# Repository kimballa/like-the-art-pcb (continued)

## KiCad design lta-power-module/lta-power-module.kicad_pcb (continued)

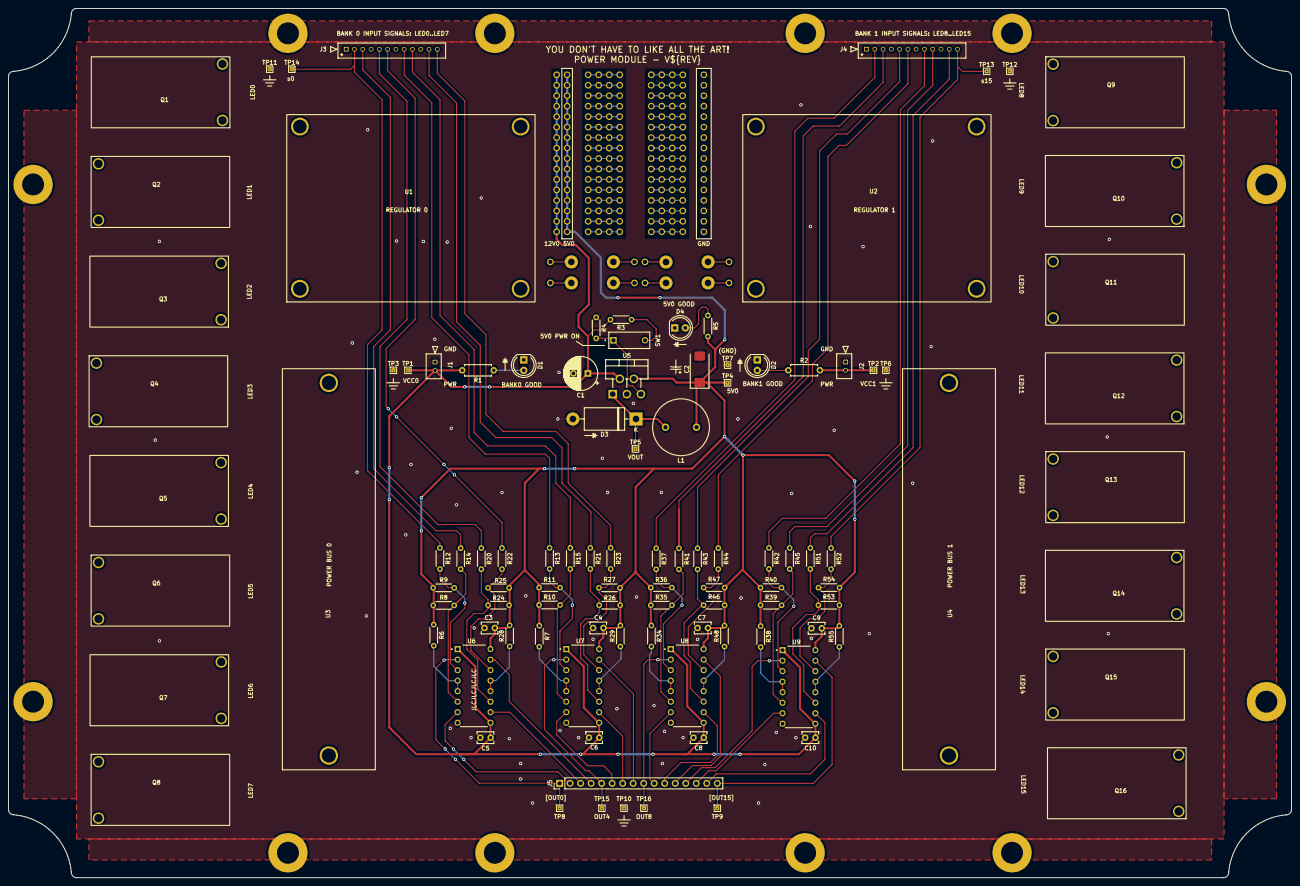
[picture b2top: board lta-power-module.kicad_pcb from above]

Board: 2 copper layers, 310.0 x 210.0 mm, 311 parts (0 on the bottom side), 106 nets.

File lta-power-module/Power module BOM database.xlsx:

Reference | Value | Footprint | Datasheet | Comment | MANUFACTURER | MPN | SPN | Supplier | Qty
C1 | 220u | Capacitor_THT:CP_Radial_D8.0mm_P3.50mm | https://content.kemet.com/datasheets/KEM_A4010_EST.pdf | 220u 20% 35V low-ESR (<=160mOhm), I_RMS>250mA aluminum | KEMET | EST227M035AG4AA | 399-6615-ND | DigiKey | 1
C2 | 68u | Capacitor_Tantalum_SMD:CP_EIA-7343-30_AVX-N_Pad2.25x2.55mm_HandSolder | https://datasheets.kyocera-avx.com/TPS.pdf | 68u 10% AVX TPS 20V low-ESR (<=150mOhm) solid tantalum; exact MPN | KYOCERA AVX | TPSD686M020R0150 | 478-9217-1-ND | DigiKey | 1
> C3-C10 | 1u | Capacitor_THT:C_Disc_D3.8mm_W2.6mm_P2.50mm | https://connect.kemet.com:7667/gateway/IntelliData-Component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 | 1u X7R 25V low-ESR THT | KEMET | C315C105K3R5TA7303 | 399-C315C105K3R5TA7303CT-ND | DigiKey | 8
D1 | PWR0 | Aaron_THT:LED_D5.0mm_SilkFix | https://cree-led.com/media/documents/C5SMF-RJF-RJE-GJF-GJE-B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 | Vf=2.0V I_test=20mA red LED 5mm THT | CreeLED | C5SMF-RJF-CT0W0BB1 | C5SMF-RJF-CT0W0BB1-ND | DigiKey | 1
D2 | PWR1 | Aaron_THT:LED_D5.0mm_SilkFix | https://cree-led.com/media/documents/C5SMF-RJF-RJE-GJF-GJE-B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 | Vf=2.0V I_test=20mA red LED 5mm THT | CreeLED | C5SMF-RJF-CT0W0BB1 | C5SMF-RJF-CT0W0BB1-ND | DigiKey | 1
D3 | SB530 | Diode_THT:D_DO-201AD_P15.24mm_Horizontal | https://www.vishay.com/docs/88721/sb520.pdf | 30V 5A Schottky diode, Vf <= 480mV. (Any SB530-xxx diode OK) | Vishay | SB530-E3/54 | SB530-E3/54GICT-ND | DigiKey | 1
D4 | 5V0PWR | Aaron_THT:LED_D5.0mm_SilkFix | https://cree-led.com/media/documents/C5SMF-RJF-RJE-GJF-GJE-B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 | Vf=2.0V I_test=20mA red LED 5mm THT | CreeLED | C5SMF-RJF-CT0W0BB1 | C5SMF-RJF-CT0W0BB1-ND | DigiKey | 1
> H1-H12 | MountingHole_Pad | MountingHole:MountingHole_5.3mm_M5_ISO7380_Pad | ~ | M5 screw mounting hole, ISO 7380 pad |  |  |  |  | 12
> J1, J2 | Molex-MicroLatch-53253-0270 | Aaron_THT:Molex-MicroLatch-53253-0270 | https://www.molex.com/webdocs/datasheets/pdf/en-us/053253027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 | 2-pin header for power (regulator out) | Molex | 532530270 | WM19004-ND | DigiKey | 2
> J3, J4 | Molex-MicroLatch-53253-1270 | Aaron_THT:Molex-MicroLatch-53253-1270 | https://www.molex.com/webdocs/datasheets/pdf/en-us/053253127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 | 12-pin signal connector | Molex | 532531270 | WM24308-ND | DigiKey | 2
J5 | Conn_01x16 | Connector_PinHeader_2.54mm:PinHeader_1x16_P2.54mm_Vertical | ~ | standard male 2.54mm gold THT header pin row | TE Connectivity AMP Connectors | 5-146858-1 | A105469CT-ND | DigiKey | 1
> J6, J8-J17, J19, J20, J22-J31, J34, J36-J45, J47, J48, J50-J59, J61-J69, J71,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 | Conn_01x01 | Aaron_Pads:1mm_PTH_No_Silk | ~ | standard 1mm PTH for prototyping |  |  |  |  | 184
> J18, J46, J60, J70, J98, J108, J122, J160 | Conn_01x01 | Aaron_Pads:1.6mm_PTH_No_Silk | ~ | larger 1.6mm holes for DO201 diodes, larger capacitors |  |  |  |  | 8
L1 | 150u | Aaron_THT:L_Radial_D13.5mm_P7.50mm | https://abracon.com/Magnetics/radial/AIUR-06.pdf | 150uH, Exact MFR/MPN required | Abracon LLC | AIUR-06-151K | 535-13029-ND | DigiKey | 1
> Q1-Q16 | Dual_MOSFET_Switch_Module | lta-power-footprints:Dual_MOSFET_Driver | https://protosupplies.com/product/high-power-dual-mosfet-swi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 | Dual MOSFET driver board w/ mounting holes |  |  | B07XJSRY6B | Amazon | 16
> R1, R2 | 1K, 1/4W | Resistor_THT:R_Axial_DIN0207_L6.3mm_D2.5mm_P7.62mm_Horizontal |  | 1K THT resistor; +/-5%; 1/4W | Stackpole | CF14JT1K00 | CF14JT1K00CT-ND | DigiKey | 2
> R3, R4 | 10K | Resistor_THT:R_Axial_DIN0204_L3.6mm_D1.6mm_P5.08mm_Horizontal | ~ | 10K THT resistor; +/-5%; 1/8W | Stackpole | CF18JT10K0 | CF18JT10K0CT-ND | DigiKey | 2
R5 | 330R | Resistor_THT:R_Axial_DIN0204_L3.6mm_D1.6mm_P5.08mm_Horizontal |  | 330R THT resistor; +/-5%; 1/8W | Stackpole | CF18JT330R | CF18JT330RCT-ND | DigiKey | 1
> R12-R15, R20-R23, R37, R41-R45, R51, R52 | 33R | Resistor_THT:R_Axial_DIN0204_L3.6mm_D1.6mm_P5.08mm_Horizontal | ~ | 33R THT resistor; +/-5%; 1/8W | Stackpole | CF18JT33R0 | CF18JT33R0CT-ND | DigiKey | 16
> R6, R7, R28, R29, R34, R38, R48, R55 | 220R | Resistor_THT:R_Axial_DIN0204_L3.6mm_D1.6mm_P5.08mm_Horizontal | ~ | 220R THT resistor; +/-5%; 1/8W | Stackpole | CF18JT220R | CF18JT220RCT-ND | DigiKey | 8
> R8-R11, R24-R27, R35, R36, R39, R40, R46, R47, R53, R54 | 2K2 | Resistor_THT:R_Axial_DIN0204_L3.6mm_D1.6mm_P5.08mm_Horizontal | ~ | 2K2 THT resistor; +/-5%; 1/8W | Stackpole | CF18JT2K20 | CF18JT2K20CT-ND | DigiKey | 16
SW1 | SW_SPST | Aaron_THT:CUI-DIP-SW_DS01-254-x-01xx | https://www.cuidevices.com/product/resource/ds01-254.pdf | Any 1x SPST THT dip switch w/ same footprint OK | CUI Devices | DS01-254-S-01BE | 2223-DS01-254-S-01BE-ND | DigiKey | 1
> TP1-TP16 | TestPoint_Flag | Aaron_THT:TestPoint_THTPad_1.0x1.0mm_Drill0.3mm | ~ |  |  |  |  |  | 16
> U1, U2 | DIYMORE_20A_Step_Down | lta-power-footprints:12V_regulator | https://www.amazon.com/dp/B07Y7YB14L?psc=1&ref=ppx_yo2ov_dt_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 |  | DIYMORE |  | B07Y7YB14L | Amazon | 2
> U3, U4 | OONO_16A_12pos_Terminal_Block | lta-power-footprints:12-way_power_distribution_bus | https://www.amazon.com/dp/B08TBXQ7H6?psc=1&smid=A2OVMUS055KM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 |  |  |  | B08TBXQ7H6 | Amazon | 2
U5 | LM2595T-5 | Aaron_THT:TO-220-5_P3.4x3.7mm_StaggerOdd_Lead3.8mm_Vertical-SilkFix | http://www.ti.com.cn/cn/lit/ds/symlink/lm2595.pdf | Exact MFR/MPN required | Texas Instruments | LM2595T-5.0/NOPB | LM2595T-5.0/NOPB-ND | DigiKey | 1
> U6-U9 | SN75374N | Aaron_TI_Parts:TI_N_R-PDIP-T16 | https://www.ti.com/lit/ds/symlink/sn75374.pdf |  | Texas Instruments | SN75374N | 296-34130-5-ND | DigiKey | 4

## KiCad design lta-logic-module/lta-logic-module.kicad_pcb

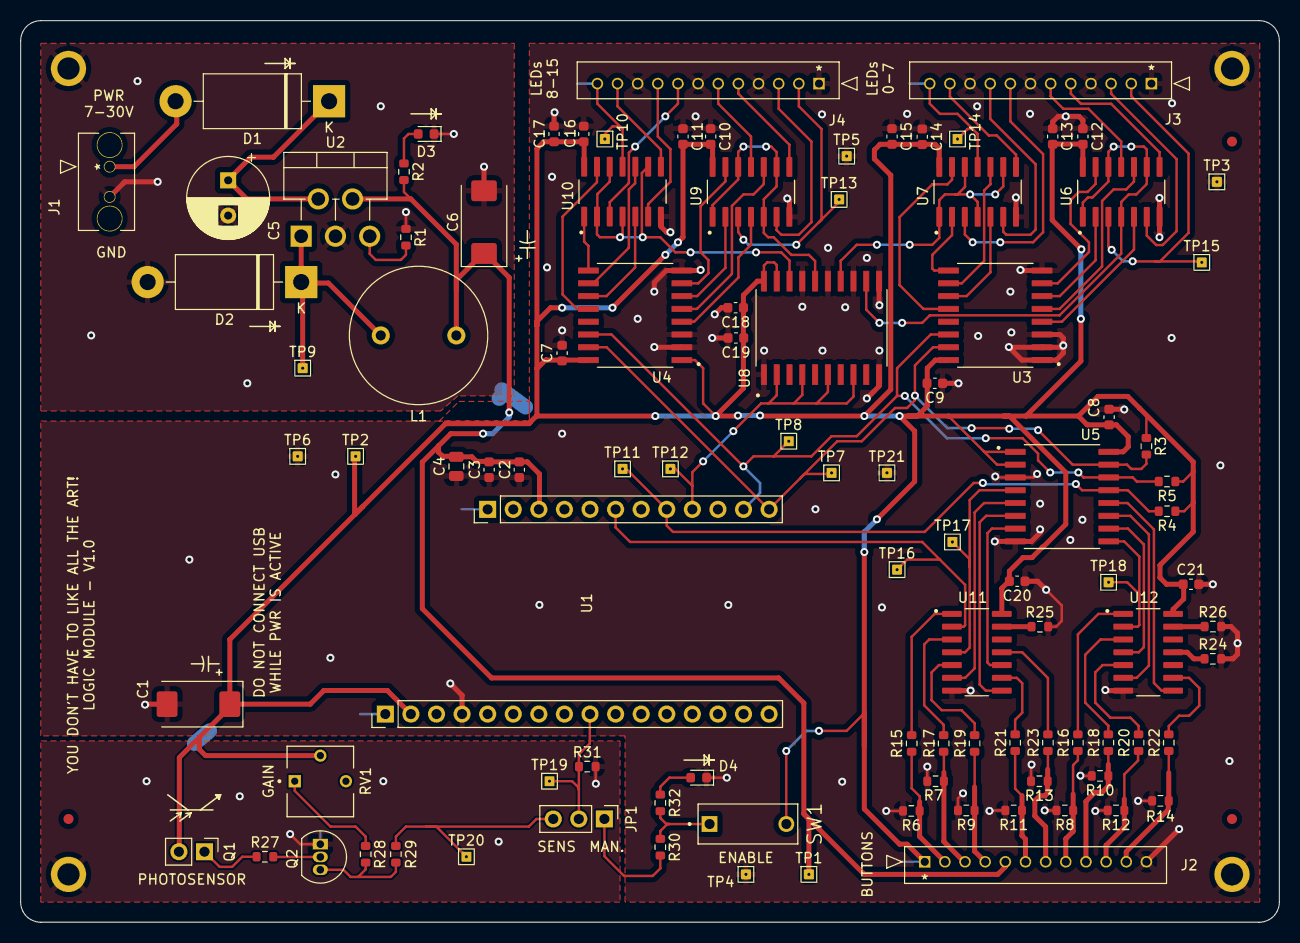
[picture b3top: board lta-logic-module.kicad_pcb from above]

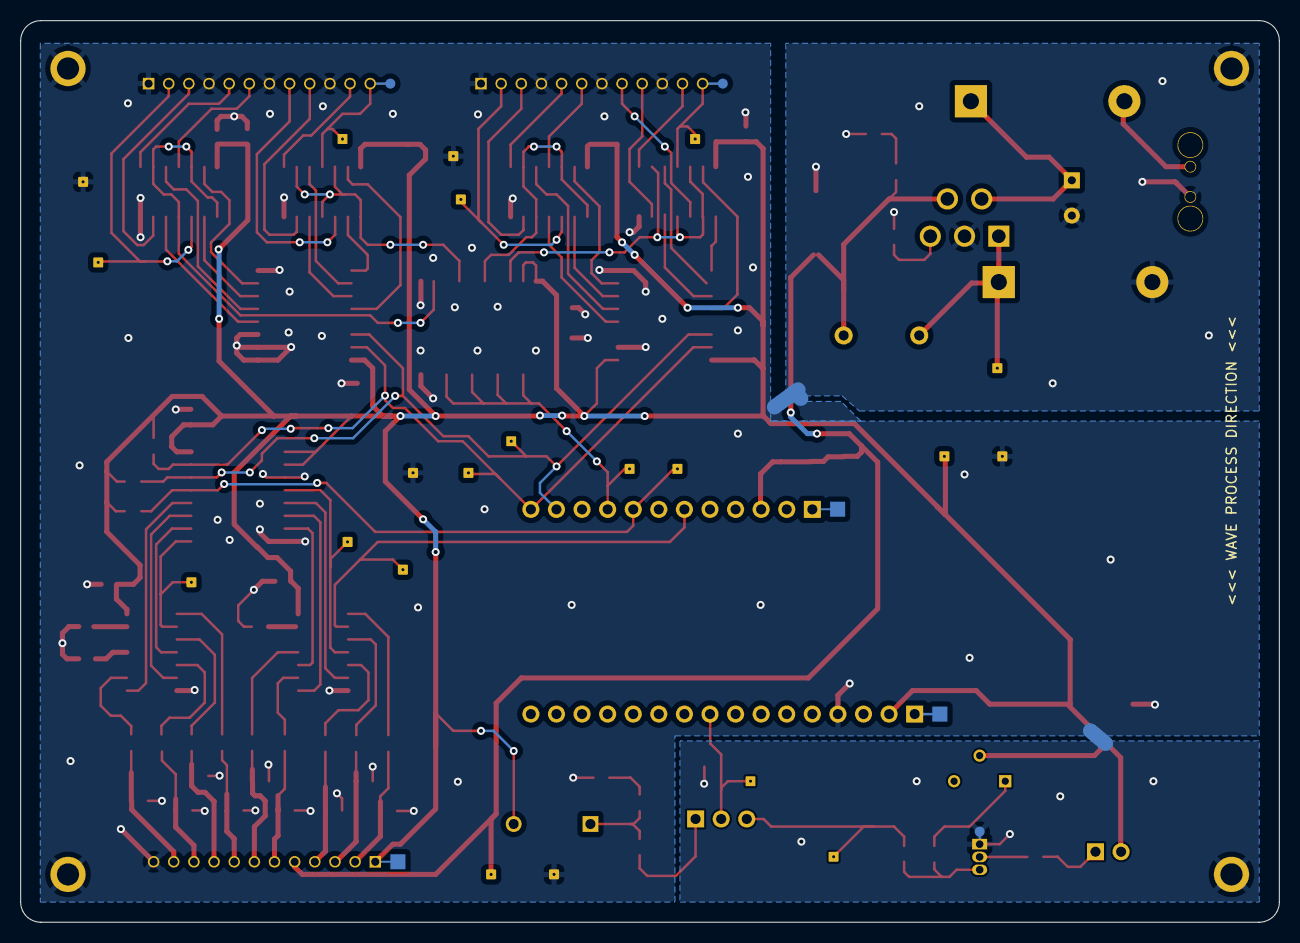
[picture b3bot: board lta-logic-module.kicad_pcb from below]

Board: 2 copper layers, 125.0 x 89.5 mm, 113 parts (6 on the bottom side), 89 nets.

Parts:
C1: 22u; CP_EIA-7343-30_AVX-N
C2, C7, C8, C9, C10, C12, C14, C16, C19, C20, C21: 100n; C_0603_1608Metric
C3, C11, C13, C15, C17, C18: 1u; C_0603_1608Metric
C4: 4u7; C_0805_2012Metric
C5: 220u; CP_Radial_D8.0mm_P3.50mm
C6: 68u; CP_EIA-7343-30_AVX-N
D1: SB5100; D_DO-201AD_P15.24mm_Horizontal
D2: SB530; D_DO-201AD_P15.24mm_Horizontal
D3: PWR; LED_0603_1608Metric
D4: DARK_EN; LED_0603_1608Metric
FID1, FID2, FID3: Fiducial; Fiducial_1mm_Mask2mm
H1, H2, H3, H4: MountingHole_Pad; MountingHole_2.2mm_M2_ISO7380_Pad
J1: Molex-MicroFit_43650-0218; Molex-Microfit-43650-0218
J2, J3, J4: Molex-MicroLatch_53253-1270; Molex-MicroLatch-53253-1270
JP1: Jumper_3_Open; PinHeader_1x03_P2.54mm_Vertical
L1: 150u; L_Radial_D13.5mm_P7.50mm
Q1: PT334-6B; PinHeader_1x02_P2.54mm_Vertical
Q2: 2N3904; TO-92_Inline
R1, R6, R7, R8, R9, R10, R11, R12, R13, R14, R24, R25, R26: 10K; R_0603_1608Metric
R2: 330R; R_0603_1608Metric
R3, R4, R5, R27, R30: 4K7; R_0603_1608Metric
R15, R16, R17, R18, R19, R20, R21, R22, R23, R28: 470R; R_0603_1608Metric
R29: 220R; R_0603_1608Metric
R31: 220K; R_0603_1608Metric
R32: 120R; R_0603_1608Metric
RV1: 25K; TRIM_3362P
SW1: SW_SPST; CUI-DIP-SW_DS01-254-x-01xx
TP1, TP2, TP3, TP4, TP5, TP6, TP7, TP8, TP9, TP10, TP11, TP12, TP13, TP14, TP15, TP16, TP17, TP18, TP19, TP20, TP21: TestPoint_Flag; TestPoint_THTPad_1.0x1.0mm_Drill0.3mm
TP22, TP23, TP26: Thief; Pad_1.5x1.5mm
TP24, TP25, TP27: Thief; Pad_D1.0mm
U1: Feather_M4_Express; Arduino_Feather_M4_Express_PinHeaders
U2: LM2595T-5; TO-220-5_P3.4x3.7mm_StaggerOdd_Lead3.8mm_Vertical-SilkFix
U3, U4, U5: PCF8574DW; TI_SOIC_DW0016A
U6, U7, U9, U10: SN74LVC00AD; TI_SOIC_D_R-PDSO-G14
U8: SN74LVC244ADWR; TI_SOIC_DW0020A
U11, U12: SN74LVC14AD; TI_SOIC_D_R-PDSO-G14

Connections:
+3V3: C1.1, C7.2, C8.2, C9.2, C10.2, C11.2, C12.2, C13.2, C14.2, C15.2, C16.2, C17.2, C18.1, C19.1, C20.2, C21.2, J2.1, Q1.2 (C), R3.1, R4.1, R5.1, RV1.2, SW1.2 (B), TP2.1, TP26.1, U1.2 (3V3), U3.16 (VDD), U4.1 (A0), U4.16 (VDD), U5.1 (A0), U5.2 (A1), U5.16 (VDD), U6.14 (VCC), U7.14 (VCC), U8.19 (~2OE), U8.20 (VCC), U9.14 (VCC), U10.14 (VCC), U11.14 (VCC), U12.14 (VCC)
+BATT: C5.1, D1.1 (K), U2.2 (VIN)
/5V0 (1A) Regulator/VOUT: D2.1 (K), L1.2, TP9.1, U2.1 (OUT)
/Button Inputs/btn_buf0: R15.2, U11.1 (1A)
/Button Inputs/btn_buf1: R17.2, U11.3 (2A)
/Button Inputs/btn_buf2: R19.2, U11.5 (3A)
/Button Inputs/btn_buf3: R21.2, U11.9 (4A)
/Button Inputs/btn_buf4: R23.2, U11.11 (5A)
/Button Inputs/btn_buf5: R16.2, U12.1 (1A)
/Button Inputs/btn_buf6: R18.2, U12.3 (2A)
/Button Inputs/btn_buf7: R20.2, U12.5 (3A)
/Button Inputs/btn_buf8: R22.2, U12.9 (4A)
/Button Inputs/btn_in0: J2.2, R6.1, R15.1
/Button Inputs/btn_in1: J2.3, R7.1, R17.1
/Button Inputs/btn_in2: J2.4, R9.1, R19.1
/Button Inputs/btn_in3: J2.6, R11.1, R21.1
/Button Inputs/btn_in4: J2.7, R13.1, R23.1
/Button Inputs/btn_in5: J2.8, R8.1, R16.1
/Button Inputs/btn_in6: J2.9, R10.1, R18.1
/Button Inputs/btn_in7: J2.10, R12.1, R20.1
/Button Inputs/btn_in8: J2.11, R14.1, R22.1
/DARK: JP1.2 (C), R31.1, TP19.1, U1.9 (A4)
/LED Signal Outputs/EN0: U6.1 (1A), U6.4 (2A), U6.9 (3A), U6.12 (4A), U8.12 (1Y4)
/LED Signal Outputs/EN1: U7.1 (1A), U7.4 (2A), U7.9 (3A), U7.12 (4A), U8.14 (1Y3)
/LED Signal Outputs/EN2: U8.16 (1Y2), U9.1 (1A), U9.5 (2B), U9.9 (3A), U9.12 (4A)
/LED Signal Outputs/EN3: U8.18 (1Y1), U10.2 (1B), U10.4 (2A), U10.9 (3A), U10.12 (4A)
/LED Signal Outputs/s0: J3.2, TP15.1, U6.3 (1Y)
/LED Signal Outputs/s1: J3.3, U6.6 (2Y)
/LED Signal Outputs/s2: J3.5, U6.8 (3Y)
/LED Signal Outputs/s3: J3.6, U6.11 (4Y)
/LED Signal Outputs/s4: J3.8, U7.3 (1Y)
/LED Signal Outputs/s5: J3.9, U7.6 (2Y)
/LED Signal Outputs/s6: J3.11, U7.8 (3Y)
/LED Signal Outputs/s7: J3.12, TP14.1, TP24.1, U7.11 (4Y)
/LED Signal Outputs/s8: J4.2, TP13.1, U9.3 (1Y)
/LED Signal Outputs/s9: J4.3, U9.6 (2Y)
/LED Signal Outputs/s10: J4.5, U9.8 (3Y)
/LED Signal Outputs/s11: J4.6, U9.11 (4Y)
/LED Signal Outputs/s12: J4.8, U10.3 (1Y)
/LED Signal Outputs/s13: J4.9, U10.6 (2Y)
/LED Signal Outputs/s14: J4.11, U10.8 (3Y)
/LED Signal Outputs/s15: J4.12, TP10.1, TP25.1, U10.11 (4Y)
/LED_EN: TP12.1, U1.20 (D6), U8.2 (1A1), U8.4 (1A2), U8.6 (1A3), U8.8 (1A4)
/Light-level sensor/DARK_SENS: JP1.3 (B), R29.2, TP20.1
/SCL: R5.2, TP8.1, U1.18 (SCL), U3.14 (SCL), U4.14 (SCL), U5.14 (SCL)
/SDA: R3.2, TP7.1, U1.17 (SDA), U3.15 (SDA), U4.15 (SDA), U5.15 (SDA)
/button0: TP16.1, U1.23 (D11), U11.2 (1Y)
/button1: TP17.1, U5.4 (P0), U11.4 (2Y)
/button2: U5.5 (P1), U11.6 (3Y)
/button3: U5.6 (P2), U11.8 (4Y)
/button4: U5.7 (P3), U11.10 (5Y)
/button5: TP18.1, U5.9 (P4), U12.2 (1Y)
/button6: U5.10 (P5), U12.4 (2Y)
/button7: U5.11 (P6), U12.6 (3Y)
/button8: U5.12 (P7), U12.8 (4Y)
/led0: U3.6 (P2), U6.2 (1B)
/led1: U3.4 (P0), U6.5 (2B)
/led2: U3.5 (P1), U6.10 (3B)
/led3: U3.7 (P3), U6.13 (4B)
/led4: U3.9 (P4), U7.2 (1B)
/led5: U3.11 (P6), U7.5 (2B)
/led6: U3.10 (P5), U7.10 (3B)
/led7: U3.12 (P7), U7.13 (4B)
/led8: U4.6 (P2), U9.2 (1B)
/led9: U4.4 (P0), U9.4 (2A)
/led10: U4.5 (P1), U9.10 (3B)
/led11: U4.7 (P3), U9.13 (4B)
/led12: U4.9 (P4), U10.1 (1A)
/led13: U4.11 (P6), U10.5 (2B)
/led14: U4.10 (P5), U10.10 (3B)
/led15: U4.12 (P7), U10.13 (4B)
/~BUTTON_INT_L: R4.2, TP11.1, U1.21 (D9), U5.13 (~INT)
GND: C1.2, C2.1, C3.1, C4.1, C5.2, C6.2, C7.1, C8.1, C9.1, C10.1, C11.1, C12.1, C13.1, C14.1, C15.1, C16.1, C17.1, C18.2, C19.2, C20.1, C21.1, D2.2 (A), D3.1 (K), D4.1 (K), H1.1, H2.1, H3.1, H4.1, J1.2, J2.12, J3.1, J3.4, J3.7, J3.10, J4.1, J4.4, J4.7, J4.10, Q2.1 (E), R1.1, R6.2, R7.2, R8.2, R9.2, R10.2, R11.2, R12.2, R13.2, R14.2, R24.2, R25.2, R26.2, R31.2, TP3.1, TP4.1, TP5.1, TP6.1, TP21.1, TP27.1, U1.4 (GND), U2.3 (GND), U3.1 (A0), U3.2 (A1), U3.3 (A2), U3.8 (VSS), U4.2 (A1), U4.3 (A2), U4.8 (VSS), U5.3 (A2), U5.8 (VSS), U6.7 (GND), U7.7 (GND), U8.1 (~1OE), U8.10 (GND), U8.11 (2A1), U8.13 (2A2), U8.15 (2A3), U8.17 (2A4), U9.7 (GND), U10.7 (GND), U11.7 (GND), U12.7 (GND)
unnamed: D1.2 (A), J1.1
unnamed: D3.2 (A), R2.1
unnamed: D4.2 (A), R32.2
unnamed: JP1.1 (A), R30.2
unnamed: Q1.1 (E), R27.1
unnamed: Q2.2 (B), R27.2
unnamed: Q2.3 (C), R28.2, R29.1
unnamed: R1.2, U2.5 (~ON/OFF)
unnamed: R24.1, U12.11 (5A)
unnamed: R25.1, U11.13 (6A)
unnamed: R26.1, U12.13 (6A)
unnamed: R28.1, RV1.1
unnamed: R30.1, R32.1, SW1.1 (A)
unnamed: TP22.1, U1.1 (RESET)
unnamed: TP23.1, U1.28 (VBATT)
VDD: C2.2, C3.2, C4.2, C6.1, J2.5, L1.1, R2.2, TP1.1, U1.26 (VUSB), U2.4 (FB)

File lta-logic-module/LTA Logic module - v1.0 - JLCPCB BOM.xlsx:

Reference | Value | Footprint | Datasheet | Comment | MANUFACTURER | MPN | SPN | Item Cost | QTY | BOM Cost
C1 | 22u | Capacitor_Tantalum_SMD:CP_EIA-7343-30_AVX-N | https://datasheets.kyocera-avx.com/X7RDielectric.pdf | 22u 10% >=16V 7343 ESR<=250mOhm solid tantalum | KYOCERA AVX | TPSD226K025R0200 | C444816 | 1.2335 | 1 | 1.2335 | SPN for 35V version; exact spec is C284839
C2, C7-C10, C12, C14, C16, C19-C21 | 100n | Capacitor_SMD:C_0603_1608Metric | https://datasheets.kyocera-avx.com/X7RDielectric.pdf | 100nF 5% 6.3V 0603 X7R ceramic; 20mOhm < ESR < 10 Ohm | KYOCERA | 06036C104JAT2A | C109474 | 5.3E-3 | 11 | 5.8299999999999998E-2 | SPN for YAEGO equiv part @ 16V
C3, C11, C13, C15, C17, C18 | 1u | Capacitor_SMD:C_0603_1608Metric | https://datasheets.kyocera-avx.com/X7RDielectric.pdf | 1u 5% 16V 0603 X7R ceramic; 20mOhm < ESR < 10 Ohm | KYOCERA | 0603YC105JAT2A | C519560 | 2.8400000000000002E-2 | 6 | 0.1704 | SPN for YAEGO equiv part
C4 | 4u7 | Capacitor_SMD:C_0805_2012Metric | https://datasheets.kyocera-avx.com/X7RDielectric.pdf | 4u7 5% 16V 0805 X7R ceramic; 20mOhm < ESR < 10 Ohm | KYOCERA | 0805YC475KAT2A | C513766 | 2.7199999999999998E-2 | 1 | 2.7199999999999998E-2 | SPN for alt. mfr; 25V 10%
C5 | 220u | Capacitor_THT:CP_Radial_D8.0mm_P3.50mm | https://content.kemet.com/datasheets/KEM_A4010_EST.pdf | 220u 20% 35V low-ESR (<=160mOhm), I_RMS>250mA aluminum | KEMET | EST227M035AG4AA | C440830 | 0.1048 | 1 | 0.1048 | SPN for Rubycon equivalent part
C6 | 68u | Capacitor_Tantalum_SMD:CP_EIA-7343-30_AVX-N | https://datasheets.kyocera-avx.com/TPS.pdf | 68u 10% AVX TPS 20V low-ESR (<=150mOhm) solid tantalum; exact MPN | KYOCERA AVX | TPSD686M020R0150 | C308898 | 2.9899 | 1 | 2.9899 | SPN for "E" case, 25V, 125 mOhm ESR (over-height; better voltage tol. / ESR; pr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
D1 | SB5100 | Diode_THT:D_DO-201AD_P15.24mm_Horizontal | https://www.smc-diodes.com/propdf/SB5100%20N0092%20REV.B.pdf | Any 100V 5A Schottky diode, Vf <= 850mV | SMC Diode Solutions | SB5100 | C154717 | 0.52829999999999999 | 1 | 0.52829999999999999
D2 | SB530 | Diode_THT:D_DO-201AD_P15.24mm_Horizontal | https://www.vishay.com/docs/88721/sb520.pdf | 30V 5A Schottky diode, Vf <= 480mV. (Any SB530-xxx diode OK) | Vishay | SB530-E3/54 | C222506 | 0.83679999999999999 | 1 | 0.83679999999999999
D3 | PWR | LED_SMD:LED_0603_1608Metric | https://media.digikey.com/pdf/Data%20Sheets/Harvatek%20PDFs/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 | Any Vf=2.0V I_test=20mA red LED OK | Harvatek | 3147-B1931URO-20D000114U1930CT-ND | C125099 | 1.7500000000000002E-2 | 1 | 1.7500000000000002E-2 | SPN for Lite-On LTST-C191KRKT
D4 | DARK_EN | LED_SMD:LED_0603_1608Metric | https://media.digikey.com/pdf/Data%20Sheets/Harvatek%20PDFs/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 | Any Vf=2.0V I_test=20mA red LED OK | Harvatek | 3147-B1931URO-20D000114U1930CT-ND | C125099 | 1.7500000000000002E-2 | 1 | 1.7500000000000002E-2 | SPN for Lite-On LTST-C191KRKT
J1 | Molex-MicroFit_43650-0218 | Aaron_THT:Molex-Microfit-43650-0218 | https://www.molex.com/pdm_docs/ps/PS-43650.pdf | Molex Micro-Fit3, 2-pin | Molex | 436500218 | DNP |  | 1 | 0
J2-J4 | Molex-MicroLatch_53253-1270 | Aaron_THT:Molex-MicroLatch-53253-1270 | https://www.molex.com/webdocs/datasheets/pdf/en-us/053253127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 | Molex Micro-Latch, 12-pin | Molex | 532531270 | DNP |  | 3 | 0
JP1 | Jumper_3_Open | Connector_PinHeader_2.54mm:PinHeader_1x03_P2.54mm_Vertical | ~ | Use 1x3 THT male pin header, gold mating, 2.54mm pitch |  |  | DNP |  | 1 | 0
L1 | 150u | Aaron_THT:L_Radial_D13.5mm_P7.50mm | https://abracon.com/Magnetics/radial/AIUR-06.pdf | 150uH, Exact MFR/MPN required | Abracon LLC | AIUR-06-151K | DNP |  | 1 | 0
Q1 | PT334-6B | Connector_PinHeader_2.54mm:PinHeader_1x02_P2.54mm_Vertical | https://media.digikey.com/pdf/Data%20Sheets/Everlight%20PDFs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 | PT334 is externally-attached; mount 1x2 pin male header (2.54mm pitch, gold) he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 |  |  | DNP |  | 1 | 0
Q2 | 2N3904 | Package_TO_SOT_THT:TO-92_Inline |  | Any 2N3904 TO-92 transistor OK | Central Semiconductor | 2N3904 PBFREE | C2081 | 3.1699999999999999E-2 | 1 | 3.1699999999999999E-2
R1, R6-R14, R24-R26 | 10K | Resistor_SMD:R_0603_1608Metric | ~ | 10K 0603 resistor; +/-1%; 1/10W | YAEGO | RC0603FR-0710KL | C25804 | 1.1999999999999999E-3 | 13 | 1.5599999999999999E-2 | SPN for JLC basic part - UNI-ROYAL equiv
R2 | 330R | Resistor_SMD:R_0603_1608Metric | ~ | 330R 0603 resistor; +/-1%; 1/10W | YAEGO | RC0603FR-07330RL | C23138 | 1.1999999999999999E-3 | 1 | 1.1999999999999999E-3 | SPN for JLC basic part - UNI-ROYAL equiv
R3-R5, R27, R30 | 4K7 | Resistor_SMD:R_0603_1608Metric | ~ | 4K7 0603 resistor; +/-1%; 1/10W | YAEGO | RC0603FR-074K7L | C23162 | 1.1999999999999999E-3 | 5 | 5.9999999999999993E-3 | SPN for JLC basic part - UNI-ROYAL equiv
R15-R23, R28 | 470R | Resistor_SMD:R_0603_1608Metric | ~ | 470R 0603 resistor; +/-1%; 1/10W | YAEGO | RC0603FR-07470RL | C23179 | 1.1999999999999999E-3 | 10 | 1.1999999999999999E-2 | SPN for JLC basic part - UNI-ROYAL equiv
R29 | 220R | Resistor_SMD:R_0603_1608Metric | ~ | 220R 0603 resistor; +/-1%; 1/10W | YAEGO | RC0603FR-07220RL | C22962 | 1.1999999999999999E-3 | 1 | 1.1999999999999999E-3 | SPN for JLC basic part - UNI-ROYAL equiv
R31 | 220K | Resistor_SMD:R_0603_1608Metric | ~ | 220K 0603 resistor; +/-1%; 1/10W | YAEGO | RC0603FR-07220KL | C22961 | 1.1999999999999999E-3 | 1 | 1.1999999999999999E-3 | SPN for JLC basic part - UNI-ROYAL equiv
R32 | 120R | Resistor_SMD:R_0603_1608Metric | ~ | 120R 0603 resistor; +/-1%; 1/10W | YAEGO | RC0603FR-07120RL | C22787 | 1.1999999999999999E-3 | 1 | 1.1999999999999999E-3 | SPN for JLC basic part - UNI-ROYAL equiv
RV1 | 25K | Aaron_THT:TRIM_3362P | https://www.bourns.com/docs/Product-Datasheets/3362.pdf | Any 25KOhm trimpot w/ same footprint OK | Bourns | 3362P-1-253LF | C81264 | 0.25869999999999999 | 1 | 0.25869999999999999 | SPN for 50 KOhm version
SW1 | SW_SPST | Aaron_THT:CUI-DIP-SW_DS01-254-x-01xx | https://www.cuidevices.com/product/resource/ds01-254.pdf | Any 1x SPST THT dip switch w/ same footprint OK | CUI Devices | DS01-254-S-01BE | C129067 | 0.2913 | 1 | 0.2913 | SPN for alt. mfr
U1 | Feather_M4_Express | aaron-imported-parts:Arduino_Feather_M4_Express_PinHeaders |  | Use 1x16 and 1x12 female THT headers, gold mating, 2.54mm pitch, 6.5--8.0mm tall |  |  | DNP |  | 1 | 0
U2 | LM2595T-5 | Aaron_THT:TO-220-5_P3.4x3.7mm_StaggerOdd_Lead3.8mm_Vertical-SilkFix | http://www.ti.com.cn/cn/lit/ds/symlink/lm2595.pdf | Exact MFR/MPN required | Texas Instruments | LM2595T-5.0/NOPB | C2868897 | 3.76 | 1 | 3.76 | no stock; can be hand-soldered @ home.
U3-U5 | PCF8574DW | Aaron_TI_Parts:TI_SOIC_DW0016A | https://www.ti.com/lit/ds/symlink/pcf8574.pdf | Exact MFR/MPN required | Texas Instruments | PCF8574DW | C7605 | 1.7708999999999999 | 3 | 5.3126999999999995 | SPN for NXP equiv; 2x-check footprint. Exact MPN is C1542490 but no stock
U6, U7, U9, U10 | SN74LVC00AD | Aaron_TI_Parts:TI_SOIC_D_R-PDSO-G14 | https://www.ti.com/lit/ds/symlink/sn74lvc00a.pdf | Exact MFR/MPN required | Texas Instruments | SN74LVC00AD | C485072 | 0.22140000000000001 | 4 | 0.88560000000000005
U8 | SN74LVC244ADWR | Aaron_TI_Parts:TI_SOIC_DW0020A | https://www.ti.com/lit/ds/symlink/sn74lvc244a.pdf | Exact MFR/MPN required; -ADW or -ADWR packaging OK. | Texas Instruments | SN74LVC244ADWR | C507250 | 0.4869 | 1 | 0.4869
U11, U12 | SN74LVC14AD | Aaron_TI_Parts:TI_SOIC_D_R-PDSO-G14 | https://www.ti.com/lit/ds/symlink/sn74lvc14a.pdf | Exact MFR/MPN required | Texas Instruments | SN74LVC14AD | C133541 | 0.21959999999999999 | 2 | 0.43919999999999998

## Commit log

2022-04-26 gitignore.
2022-04-26 Empty schematic.
2022-04-26 Start sketching out schematic.
    Add layout for Quad LED Driver.
    Add placeholders for other subcircuits.
2022-04-30 Add schematic for button inputs and I2C signal busses.
    * Define 9x button inputs
    * Define I2C parallel bus expanders used for FET output signals
    and button inputs
    * Add (empty) schematic for 5V switching regulator.
2022-04-30 Add PI3740-based prototype 12V buck/boost regulator.
    Add 12V buck/boost regulator schematic based on 3x PI3740 regulators.
    Each PI3740 can deliver 6A.
    This circuit was intended for operation with VIn = 11.5--14.4V
    and not used after I switched to VIn centered at 24V.
2022-04-30 A bit more cleanup on that older 12V regulator
2022-04-30 Clear the decks for new 12V regulator design
2022-05-02 Sketch out ISL8117-driven 12V regulator.
    Another candidate entry for on-board 12V regulation is to
    build our own based on the reference schematic from the ISL8117
    DC buck regulator controller datasheet.
    Implemented (most of) this reference schematic here.
2022-05-02 Move "like-the-art" into logic-module subproject.
2022-05-02 Make copy of schematics as lta-power-module.
    Make separate KiCAD projects for LTA "logic" and "power" modules
    which will be on separate PCBs.
2022-05-03 Full sketch of logic module schematic.
    - Add button inputs
    - Add LED signal driver / PWM combination
    - Add 5V regulator based on LM2592
2022-05-03 Fix ERC violations.
2022-05-03 Add TODOs, update some footprints.
2022-05-03 Initial PCB setup
    * Configure Elecrow DRC checks for lta-logic-module.
    * Switch SN74LVC244A from 'N' PDIP to 'DWR' SOIC footprint.
2022-05-04 Add light sensor circuit.
    Adjust TODOs and comments after testing btn circuit.
2022-05-05 Add main draft of PCB layout for logic module.
2022-05-06 Fix all the footprint data.
    Somehow my footprint info got clobbered. Reset a bunch of symbol
    properties to empty... this info is now all back in place.
    * Added 3 fiducial marks
    * Added 4 mounting holes
2022-05-06 More unfucking.
2022-05-06 Switch 12-pin headers to Molex Micro-Latch c'tors.
2022-05-06 Re-establish symbol properties.
2022-05-06 Connect new J3--5 footprints to traces.
2022-05-06 All DRC checks passing.
2022-05-06 Update some footprints to be more accurate.
2022-05-06 Relocated optosensor to south side of board.
    * Moved optosensor logic away from the USB plug-side of the Feather.
    You can now plug in USB while the Feather is attached to the board.
    * Changed schematic such that `button0` now goes directly to the
    Feather; buttons 1--8 are on the I2C bus. Cleans up some obnoxious
    routing.
    * Optimized other routing & GND fill.
2022-05-07 Add test points
2022-05-08 Final tweaks before RTM.
2022-05-08 Isolated ground planes for AGND and DGND.
    * Analog optosensor now has isolated ground plane area.
    * Moved 3V3 load capacitor behind U1 to keep its return
    fully on digital ground.
2022-05-08 Fix GND path return.
    * Route power traces over ground plane.
    * Add routed corners to edge cuts
    * Remove final TODO notes.
2022-05-08 Add indicator LED to SW1 enabled.
    Adds 220K pull-down resistor to DARK signal. (Validated.)
    Update solder thief pads and process direction indicator.
2022-05-08 Generate logic module 2022-05-08 v1.0 fab documentation.
2022-05-09 Clear out power module schematic.
2022-05-09 Power module main electrical schematic drawn, unannotated.
    A logical schematic including flying wire connections between off-board
    modules is sketched in the associated pptx file.
2022-05-09 Small sheet cleanup.
2022-05-10 Add custom footprints for 12V regulator and power distribution bus.
2022-05-10 Remove unnecessary LEDs.
    The MOSFET drivers have LEDs which will operate based on the gate
    signal alone; we can just rely on those.
2022-05-10 small cleanup.
2022-05-10 Add dual mosfet driver footprint & model.
2022-05-11 Considerably more work on power module PCB.
    * Slight reorganization of layout.
    * Routed all traces.
2022-05-11 Add protoboard.
2022-05-11 Work on border.
    * Add perimeter edge cut to fit WH-22 polycase.
    * Add M5 mounting holes in temp locations on PCB.
    * Lay out and lock left-edge M5 mounting holes.
2022-05-15 Lay out all mounting holes.
    * All DRC checks passing.
    * Fix footprint silkscreen conflicts.
    * Fix ext. regulator module symbol.
2022-05-15 NPTHs and test points.
    * Added NPTH defs to `User.Eco1` layer in footprints.
    * Renamed `User.Eco1` to `Mechanical` in PCB layout.
    * Duplicated `Edge Cuts` onto `Mechanical` layer.
    *Use `Mechanical` as `.GKO` layer, not `Edge Cuts`!*
    * Added test points for key signals.
2022-05-15 Update module footprints to be more accurate.
2022-05-16 Add schematic for photodiode simulation.
2022-05-16 Further refinement of potentiometer model.
2022-05-16 Open solder masks up around mounting holes.
2022-05-16 Switched to plated through-holes for all mounting.
    Ready for release to manufacturing.
2022-05-16 Add power module production gerbers for v1.0 RTM.
2022-05-16 misc final data cleanup
2022-05-16 Check in power module BOM spreadsheet.
2022-05-16 Add top-level README.
    * Copy logic module BOM from only in finished fab-run folder to have a
    working copy in the logic module working dir.
    * Add rendered views of power module 1.0 PCB and PCBA.
2022-06-04 metadata changes.
2022-06-04 Create new 'mosfet-chip' pcb subproject.
    The Power MOSFET daughter boards I purchased were too unreliable
    to use in production. I need to make one with a similar schematic
    but assembled with higher-quality components.
2022-06-04 First draft schematic & PCB for mosfet chip.
2022-06-04 Add LED; use SMT for passives; fill zones.
2022-06-04 Update part numbers for JLC assembly.
2022-06-05 MOSFET Chip ready for RTM.
    * Change screw terminal to Phoenix Contact MPN 1711725.
    * Add appropriately-sized thermal reliefs to pads in pour zones.
    * VArious small tweaks, silkscreen adjustments, etc.
2022-06-05 Update board for D4M.
    * Fix layout violation: Move SMT components 2.5mm+ from edge.
    * Update MPN/SPNs for resistors to use correct JLC basic library parts.
2022-06-05 Tiny zone fill nudge.
2022-06-05 Move traces to more gracefully handle mouse bites
2022-06-05 Small routed fillet on corners.
2022-06-05 Add BOM file.
2022-06-05 Add panelizer export for RTM.
    Ready (again?) for RTM; added panelized 2x3 PCB for MOSFET Chip.
2022-06-05 MOSFET Chip 2x3 Panel RTM.
2022-06-20 Update logic module power budget from button LED measurements.
    Button LEDs draw ~11mA each (98 mA total) empirically; not the ~20mA each
    I initially guessed for estimating purposes.
2022-07-03 Add version of logic module bom w/ JLCPCB's SPNs.
    If I want to re-fab the logic module, refer to the LCSC SPNs in
    the "JLCPCB BOM" file to do PCBA at JLC for much cheaper than
    Elecrow.
2022-07-03 Unknown power module BOM xlsx change.
2022-08-08 Add more readme for mosfet-chip.
2022-08-08 Clarification in readme
2022-08-09 Logic Mod: Add self-test switch; bump to v1.1 for development.
    * Add a push-button (SPST, NO) switch wired from Arduino D4 to GND to
    trigger admin mode and start a self-test cycle.
    This has been retrofitted on the active board via rework but could be
    integrated on the PCB for v1.1.
    * Version number incremented to 1.1 for next development cycle
    * Release date set to unreleased.
